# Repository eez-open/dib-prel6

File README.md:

### Ownership and License
The contributors are listed in CONTRIB.TXT. This project uses the TAPR v1.0 license, see LICENSE.TXT.

### Description

The EEZ DIB PREL6 module features six independently programmable power relays.

### Feature list

* On-board STM32F030C6T6 or STM32F031C4T6 MCU
* 2 x 16-pin dual row 3.81 mm connectors
* 4 x SPDT relays, max. 8 A / 230 Vac
* 2 x SPST relays, max. 8 A / 230 Vac
* On-board +3.3 V LDO
* Firmware download via UART
* Optional SWD for debugging
* I2C EEPROM for storing board specific parameters
* Dimensions: 146 x 95 mm, 2-layer PCB

### Firmware repository

https://github.com/eez-open/dib-prel6-fw
The firmware download procedure is described in the User Manual in [Chapter 13](https://github.com/eez-open/modular-psu/blob/master/docs/user%20manual/EEZ%20BB3%20user%20manual.pdf). 

### r1B2 prototype

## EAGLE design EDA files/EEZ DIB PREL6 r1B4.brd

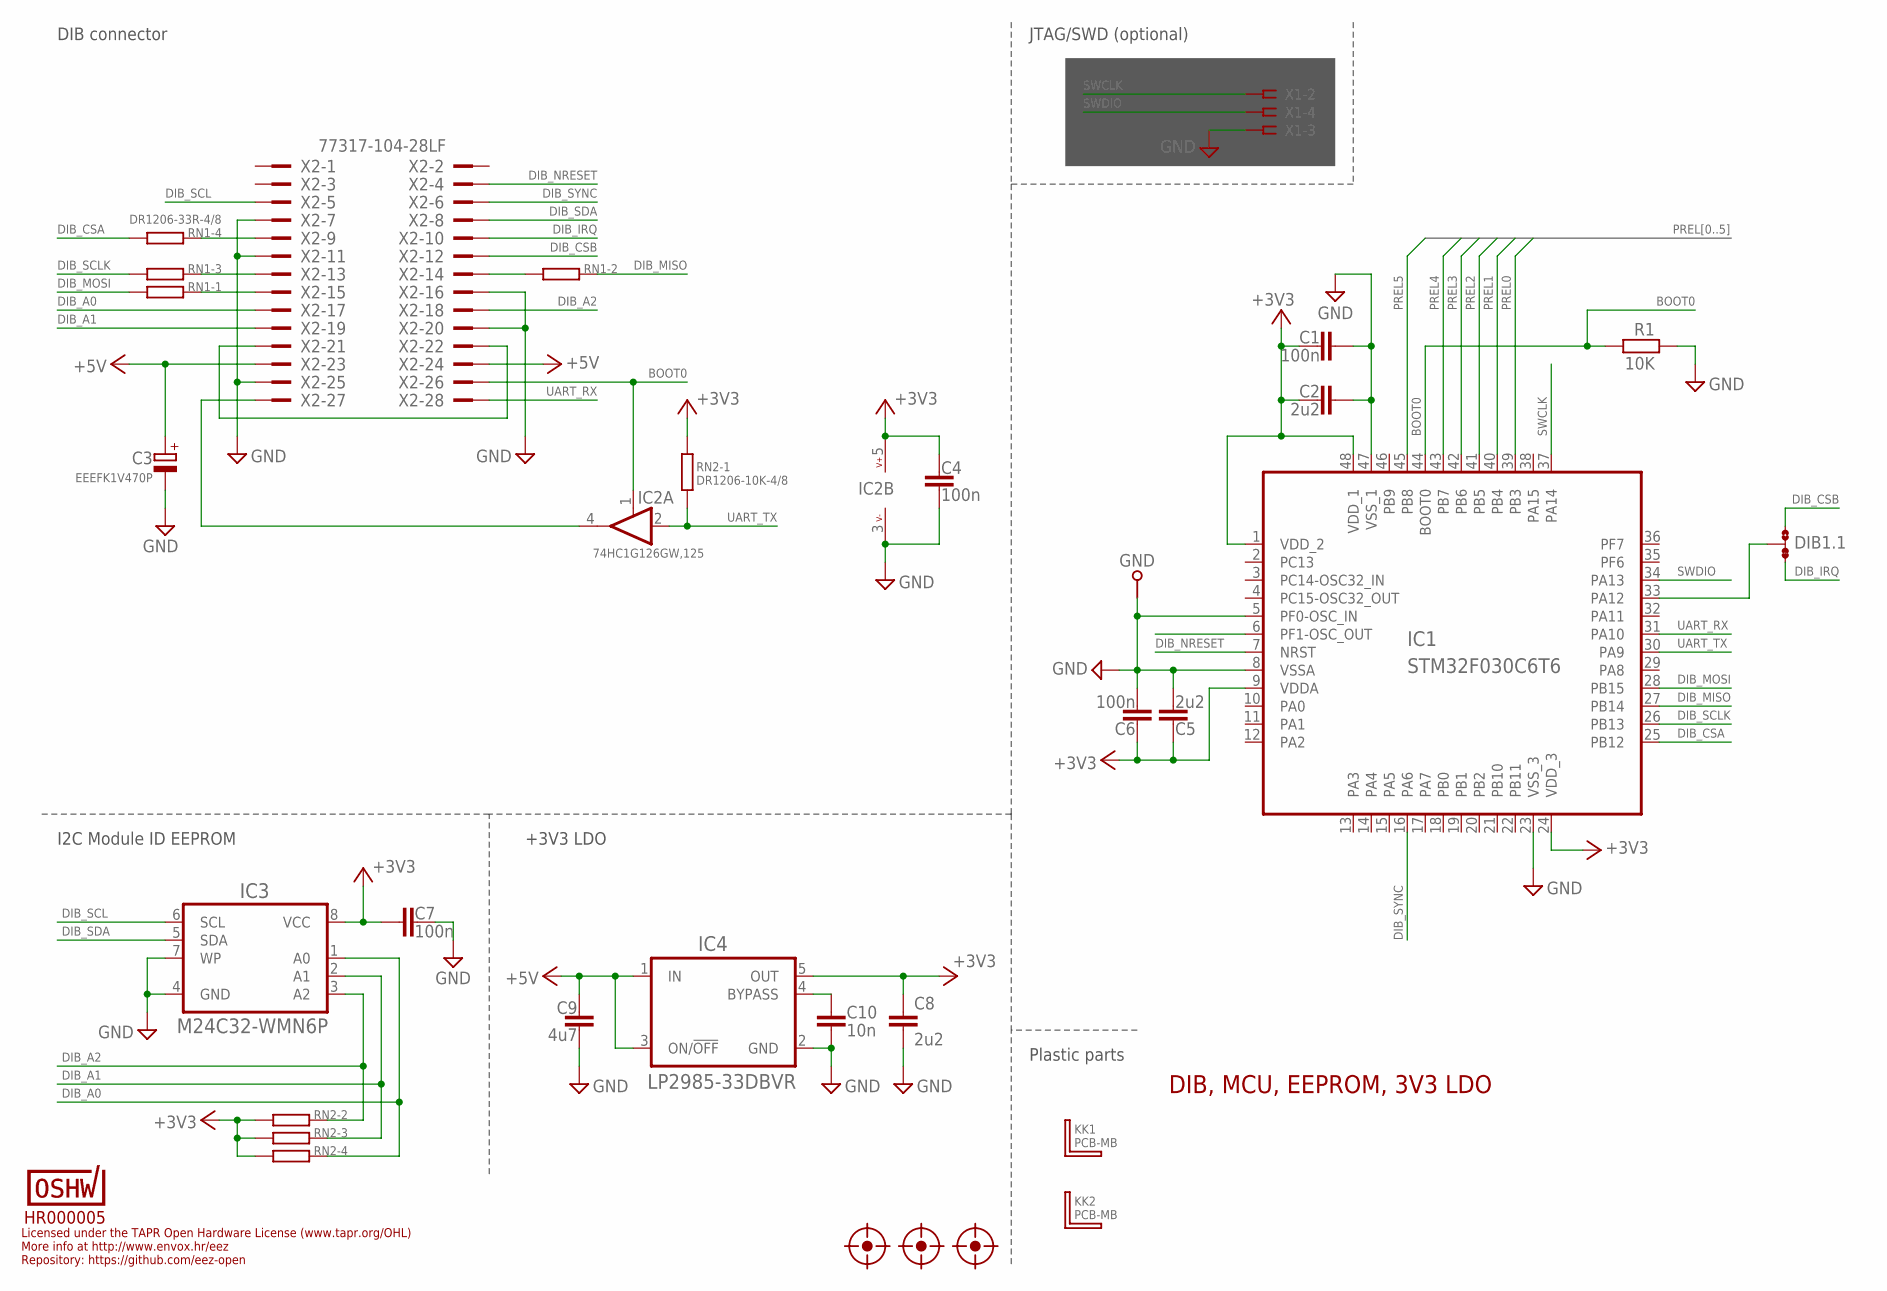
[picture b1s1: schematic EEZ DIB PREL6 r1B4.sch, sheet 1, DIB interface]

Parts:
C1, C4, C6, C7: 100n; C0603
C2, C5, C8: 2u2; C0805
C3: EEEFK1V470P; CAPAE660X610N
C9: 4u7; C0805
C10: 10n; C0805
DIB1.1: JP3-CUT-0805-ROTATED; JP3-0805-CUT2
FM1, FM2, FM3: FIDUCIAL_2; FIDUCIAL_DUAL
GND: PCB_TEST_TABSHIELD; PCB_SHIELD_TAB
IC1: STM32F030C6T6; LQFP-48
IC2: 74HC1G126GW,125; SOT65P210X110-5N
IC3: M24C32-WMN6P; SOIC127P600X173-8N
IC4: LP2985-33DBVR; SOT95P270X145-5N
KK1, KK2: PCB-MB
R1: 10K; R0805
RN1: DR1206-33R-4/8; CAY16
RN2: DR1206-10K-4/8; CAY16
U$3: HR000005; CERT-SMALL-SILK
X1: N.C.; SSW-106-02-S-S
X2: 77317-104-28LF

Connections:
+3V3: C1.2, C2.1, C4.1, C5.2, C6.1, C7.2, C8.1, IC1.1 (VDD_2), IC1.9 (VDDA), IC1.24 (VDD_3), IC1.48 (VDD_1), IC2.5 (V+), IC3.8 (VCC), IC4.5 (OUT), RN2.5 (2), RN2.6 (2), RN2.7 (2), RN2.8 (2)
+5V: C3.1 (+), C9.2, IC4.1 (IN), IC4.3 (ON/!OFF), X2.23, X2.24; also elsewhere on the board
BOOT0: IC1.44 (BOOT0), IC2.1 (EN), R1.2, X2.26
DIB_A0: IC3.1 (A0), RN2.4 (1), X2.17
DIB_A1: IC3.2 (A1), RN2.3 (1), X2.19
DIB_A2: IC3.3 (A2), RN2.2 (1), X2.18
DIB_CSA: IC1.25 (PB12), RN1.4 (1)
DIB_CSB: DIB1.1.NO, X2.12
DIB_IRQ: DIB1.1.NC, X2.10
DIB_MISO: IC1.27 (PB14), RN1.2 (1)
DIB_MOSI: IC1.28 (PB15), RN1.1
DIB_NRESET: IC1.7 (NRST), X2.4
DIB_SCL: IC3.6 (SCL), X2.5
DIB_SCLK: IC1.26 (PB13), RN1.3 (1)
DIB_SDA: IC3.5 (SDA), X2.8
DIB_SYNC: IC1.16 (PA6), X2.6
DIB_UART_RX: IC2.4 (O), X2.27
GND: C1.1, C2.2, C3.2 (-), C4.2, C5.1, C6.2, C7.1, C8.2, C9.1, C10.1, GND.1, IC1.5 (PF0-OSC_IN), IC1.8 (VSSA), IC1.23 (VSS_3), IC1.47 (VSS_1), IC2.3 (V-), IC3.4 (GND), IC3.7 (WP), IC4.2 (GND), R1.1, X1.3, X2.7, X2.11, X2.16, X2.20, X2.25; also elsewhere on the board
unnamed: X2.21, X2.22
unnamed: DIB1.1.COM, IC1.33 (PA12)
unnamed: RN1.5 (2), X2.9
unnamed: C10.2, IC4.4 (BYPASS)
unnamed: RN1.6 (2), X2.13
unnamed: RN1.7 (2), X2.14
unnamed: RN1.8 (2), X2.15
PREL0: IC1.39 (PB3); also elsewhere on the board
PREL1: IC1.40 (PB4); also elsewhere on the board
PREL2: IC1.41 (PB5); also elsewhere on the board
PREL3: IC1.42 (PB6); also elsewhere on the board
PREL4: IC1.43 (PB7); also elsewhere on the board
PREL5: IC1.45 (PB8); also elsewhere on the board
SWCLK: IC1.37 (PA14), X1.2
SWDIO: IC1.34 (PA13), X1.4
UART_RX: IC1.31 (PA10), X2.28
UART_TX: IC1.30 (PA9), IC2.2 (I), RN2.1

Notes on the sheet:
Licensed under the TAPR Open Hardware License (www.tapr.org/OHL)
Repository: https://github.com/eez-open
More info at http://www.envox.hr/eez
DIB, MCU, EEPROM, 3V3 LDO
Plastic parts
I2C Module ID EEPROM
+3V3 LDO
JTAG/SWD (optional)
DIB connector

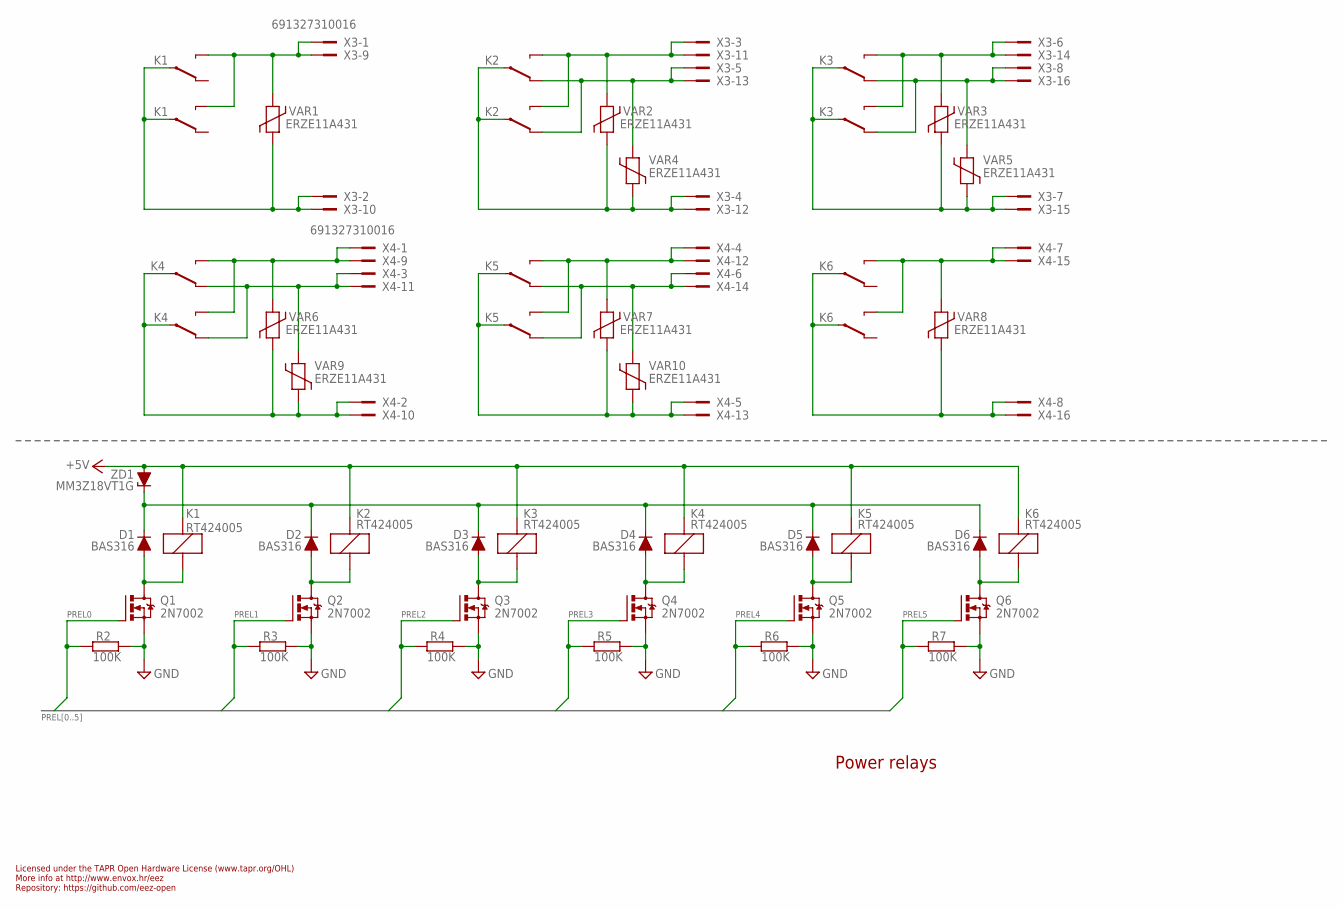
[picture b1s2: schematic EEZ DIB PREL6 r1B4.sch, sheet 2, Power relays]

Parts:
D1, D2, D3, D4, D5, D6: BAS316; SOD323-R
K1, K2, K3, K4, K5, K6: RT424005; RT-C/016A5_ROUND
Q1, Q2, Q3, Q4, Q5, Q6: 2N7002; SOT103P240X110-3N; MPN 2N7002-7-F
R2, R3, R4, R5, R6, R7: 100K; R0805
VAR1, VAR2, VAR3, VAR4, VAR5, VAR6, VAR7, VAR8, VAR9, VAR10: ERZE11A431; VARISTOR_13MM
X3, X4: 691327310016
ZD1: MM3Z18VT1G; SOD323-R

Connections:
+5V: K1.A2 (C1), K2.A2 (C1), K3.A2 (C1), K4.A2 (C1), K5.A2 (C1), K6.A2 (C1), ZD1.A; also elsewhere on the board
GND: Q1.2 (S), Q2.2 (S), Q3.2 (S), Q4.2 (S), Q5.2 (S), Q6.2 (S), R2.2, R3.2, R4.2, R5.2, R6.2, R7.2; also elsewhere on the board
unnamed: D4.A, K4.A1 (C2), Q4.3 (D)
unnamed: D1.A, K1.A1 (C2), Q1.3 (D)
unnamed: D1.C, D2.C, D3.C, D4.C, D5.C, D6.C, ZD1.C
unnamed: D2.A, K2.A1 (C2), Q2.3 (D)
unnamed: D3.A, K3.A1 (C2), Q3.3 (D)
unnamed: D5.A, K5.A1 (C2), Q5.3 (D)
unnamed: K4.12A (S), K4.12B (S), VAR9.2, X4.3, X4.11
unnamed: K4.14A (O), K4.14B (O), VAR6.2, X4.1, X4.9
unnamed: K5.12A (S), K5.12B (S), VAR10.2, X4.6, X4.14
unnamed: K4.11A, K4.11B, VAR6.1, VAR9.1, X4.2, X4.10
unnamed: K5.14A (O), K5.14B (O), VAR7.2, X4.4, X4.12
unnamed: K1.14A (O), K1.14B (O), VAR1.2, X3.1, X3.9
unnamed: K5.11A, K5.11B, VAR7.1, VAR10.1, X4.5, X4.13
unnamed: K6.14A (O), K6.14B (O), VAR8.2, X4.7, X4.15
unnamed: K1.11A, K1.11B, VAR1.1, X3.2, X3.10
unnamed: K6.11A, K6.11B, VAR8.1, X4.8, X4.16
unnamed: K2.14A (O), K2.14B (O), VAR2.2, X3.3, X3.11
unnamed: K2.11A, K2.11B, VAR2.1, VAR4.1, X3.4, X3.12
unnamed: K2.12A (S), K2.12B (S), VAR4.2, X3.5, X3.13
unnamed: K3.14A (O), K3.14B (O), VAR3.2, X3.6, X3.14
unnamed: K3.11A, K3.11B, VAR3.1, VAR5.1, X3.7, X3.15
unnamed: K3.12A (S), K3.12B (S), VAR5.2, X3.8, X3.16
unnamed: D6.A, K6.A1 (C2), Q6.3 (D)
PREL0: Q1.1 (G), R2.1; also elsewhere on the board
PREL1: Q2.1 (G), R3.1; also elsewhere on the board
PREL2: Q3.1 (G), R4.1; also elsewhere on the board
PREL3: Q4.1 (G), R5.1; also elsewhere on the board
PREL4: Q5.1 (G), R6.1; also elsewhere on the board
PREL5: Q6.1 (G), R7.1; also elsewhere on the board

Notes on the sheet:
Licensed under the TAPR Open Hardware License (www.tapr.org/OHL)
Repository: https://github.com/eez-open
More info at http://www.envox.hr/eez
Power relays

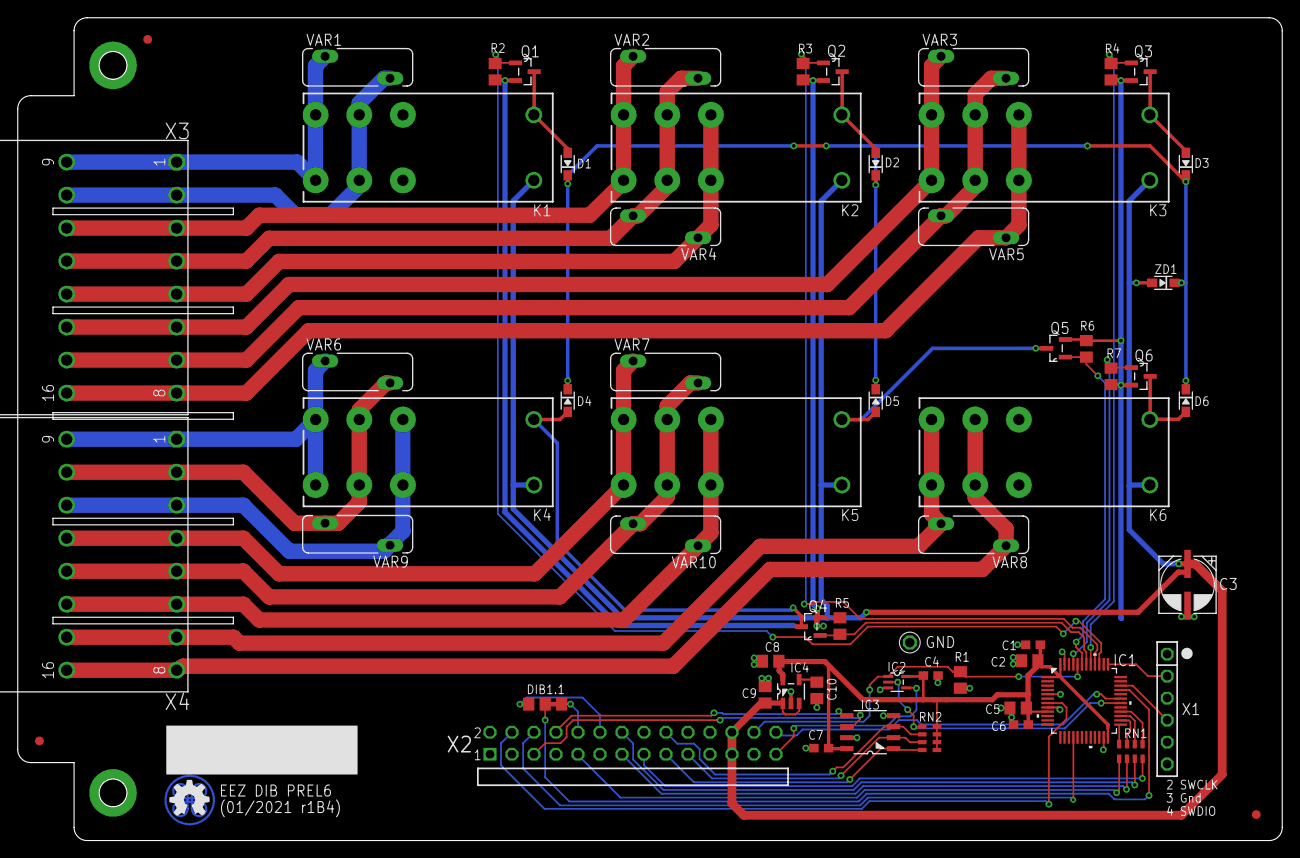
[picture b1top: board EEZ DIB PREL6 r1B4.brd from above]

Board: 2 copper layers, 146.0 x 95.0 mm, 65 parts (1 on the bottom side), 58 nets.

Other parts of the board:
EEZ_SIGNATURE: SIGNATURESMALL; SIGNATURE_5MM

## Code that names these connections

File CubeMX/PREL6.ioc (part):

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Mcu.Name=STM32F030C6Tx
Mcu.Package=LQFP48
Mcu.UserName=STM32F030C6Tx
PA10.Mode=Asynchronous
PA10.Signal=USART1_RX
PA12.GPIOParameters=GPIO_Label
PA12.GPIO_Label=DIB_IRQ
PA12.Signal=GPIO_Output
PA13.Mode=Serial_Wire
PA13.Signal=SYS_SWDIO
PA14.Mode=Serial_Wire
PA14.Signal=SYS_SWCLK
PA6.GPIOParameters=GPIO_Label
PA6.GPIO_Label=DIB_SYNC
PA6.Signal=GPIO_Input
PA9.Mode=Asynchronous
PA9.Signal=USART1_TX
PB12.GPIOParameters=GPIO_Label
PB12.GPIO_Label=DIB_CSA
PB12.Mode=NSS_Signal_Hard_Input
PB12.Signal=SPI1_NSS
PB13.GPIOParameters=GPIO_Label
PB13.GPIO_Label=DIB_SCLK
PB13.Mode=Full_Duplex_Slave
PB13.Signal=SPI1_SCK
PB14.GPIOParameters=GPIO_Label
PB14.GPIO_Label=DIB_MISO
PB14.Mode=Full_Duplex_Slave
PB14.Signal=SPI1_MISO
PB15.GPIOParameters=GPIO_Label
PB15.GPIO_Label=DIB_MOSI
PB15.Mode=Full_Duplex_Slave
PB15.Signal=SPI1_MOSI
PB3.GPIOParameters=GPIO_Label
PB3.GPIO_Label=PR0
PB3.Signal=GPIO_Output
PB4.GPIOParameters=GPIO_Label
PB4.GPIO_Label=PR1
PB4.Signal=GPIO_Output
PB5.GPIOParameters=GPIO_Label
PB5.GPIO_Label=PR2
PB5.Signal=GPIO_Output
PB6.GPIOParameters=GPIO_Label
PB6.GPIO_Label=PR3
PB6.Signal=GPIO_Output
PB7.GPIOParameters=GPIO_Label
PB7.GPIO_Label=PR4
PB7.Signal=GPIO_Output
PB8.GPIOParameters=GPIO_Label
PB8.GPIO_Label=PR5
PB8.Signal=GPIO_Output
board=custom

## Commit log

2020-02-14 readme.me update
2020-02-15 MCU .ioc update
2020-02-17 BOM added, improved PCB clearances
2020-02-22 UART relocated
2020-02-26 debug connector update
2020-02-28 PCB terminals position adjusted
2020-02-29 IC2 package update
2020-03-19 front panel connectors position adjusted
2020-04-04 #1 fixed
2020-05-04 swap UART TX and RX
2020-05-18 prototype picture
2020-06-12 IRQ selection jumper
2020-09-22 prototype r1B2 image
2020-12-02 #4, OSHW UID
2020-12-13 added link to firmware repository
2021-01-30 PCB ID added
2021-01-31 BOM update
2021-03-25 Module front mask, centroid files

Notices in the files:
parts and their libraries:
EEZ_DIB: This work is licensed under the TAPR Open Hardware License.
